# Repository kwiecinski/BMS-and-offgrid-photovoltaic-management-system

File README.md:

# Offgrid Photovoltaic Management System 
 ### Project contains:
 #### A. Power and mechanical part:

  1. [ Photovoltaic modules](#1-photovoltaic-modules)  
  2. [ Concrete base mounting](#2-concrete-base-mounting)  
  3. [ Metalworking and welding mounting bases and angle bar](#3-metalworking-and-welding-mounting-bases-and-angle-bar)  
  4. [ Painting mounting base, angle bars and perforated profiles](#4-painting-mounting-base-angle-bars-and-perforated-profiles)  
  5. [ PV mountings to perforated profiles](#5-pv-mountings-to-perforated-profiles)  
  6. [ Assembly of PV installation](#6-assembly-of-pv-installation)  
  7. [ Fully assembled PV installation](#7-fully-assembled-pv-installation)<br>
  8. [ Underground Cable Installation and Connection to the Building](#8-underground-cable-installation-and-connection-to-the-building)
 
B. [EASUN inverter - description, installation schematic and wiring](#easun-inverter---description-installation-and-wiring)
#### C. Managemenet system part:
- [BMS for lead-acid batteries](#bms-for-lead-acid-batteries) - equalize battery, protect from large charge/discharge currents, montors battery state (temp, voltage)
- [ESP32 Master module](#esp32-master-module) - it communicate with EASUN  converter, BMS, Homa Assistant, Energy Meters and sensor. Supervise all system work propertly.
- [Home Assistant integration](#home-assistant-integration) - integrate ESP Master module with HA for easy and compact managment (local and remote access)
- [Power Tracking module](#power-tracking-module) - it is used to regulate heater power accordingly to avaible energy from PV

## PV panels connection and DIY Ground Mount structure 

### 1. Photovoltaic modules
The photovoltaic modules I used in my PV installation are Trina Solar TSM-245. These are used panels that I purchased for around $40 each. The installation consists of 8 modules connected in series.

[📄 **Trina Solar TSM-245 datasheet**](docs/datasheets/TSM-PC05_trinasolar.pdf)

<table>
  <tr>
    <td align="center">
      <br />
      <sub>PV module TSM-245 - technical data</sub>
    </td>
    <td align="center">
      <br />
      <sub>PV module TSM-245 - internal diode wiring</sub>
    </td>
  </tr>
</table>

<table>
  <tr>
    <td align="center">
      <br />
      <sub>PV module TSM-245 - front</sub>
    </td>
    <td align="center">
      <br />
      <sub>PV module TSM-245 - back</sub>
    </td>
  </tr>
</table>

The first stage was marking the mounting points for the mouting base structure. The entire construction has eight support points. After digging holes in the ground, they were filled with concrete, and concrete bases with reinforcement were embedded in them. I had plenty of these as production waste from the company where I work. They are typically used for mounting lightning protection masts on flat building roofs.

Inside each base, there is reinforcement and four M16 threads. I modified the bases by drilling holes on the opposite side, and I welded additional reinforcement to the bottom using scrap metal, which helps to improve the structural stability.

Before mounting the structure to the concrete bases, the contact surfaces were coated with a bituminous compound to prevent corrosion.

### 2. Concrete base mounting

<table>
  <tr>
    <td align="center" colspan="2">
      <br />
      <sub>Concrete base with reinforcement</sub>
    </td>
  </tr>
  <tr>
    <td align="center">
      <br />
      <sub>Concrete base with mounting thread</sub>
    </td>
    <td align="center">
      <br />
      <sub>Concrete base with bitumen</sub>
    </td>
  </tr>
</table>
<br>

Visible in the photo below is a set of four steel mounting bases of varying heights, with welded pipes and mounting plates. Each element was made with consideration for uneven ground, that is why there are different pipe lengths. Each base has a bottom plate with holes for M16 bolts, intended for anchoring to a concrete base. On the table next to them lies a long steel angle bar, which was welded from several sections. After welding, the elements were ground down. The photo was taken after the mechanical work was completed, during surface preparation for painting. 
All the steel used for building the PV mouting structure comes from scrap yard.

### 3. Metalworking and welding mounting bases and angle bar
<br>
<table>
  <tr>
    <td align="center" colspan="2">
      <br />
      <sub>Metalworking and welding mounting bases and angle bar</sub>
    </td>
  </tr>
  <tr>
    <td align="center" colspan="2">
      <br />
      <sub>Steel angle bar before painting</sub>
    </td>
  </tr>
    <tr>
    <td align="center" colspan="2">
      <br />
      <sub>Longer mounting base  while painting</sub>
    </td>
  </tr>
</table>

Longer mounting base are responsible for the solar incidence angle which in this case is 40 degrees
### 4. Painting mounting base, angle bars and perforated profiles
<table>
  <tr>
    <td align="center" colspan="2">
      <a href="docs\photos\ground-mount-structure\steel-workshop-and-painting-11.jpg">
        
      <div style="width: 200px;">
        
        <div style="text-align: center;">
          <sub>Shorter and longer mounting base after painting</sub>
        </div>
      </div>
    </td>
  </tr>
  <tr>
    <td colspan="2" style="text-align: left;">
      <div style="width: 410px;">
        
        <div style="text-align: center;">
          <sub>Shorter mounting base after painting</sub>
        </div>
      </div>
    </td>
  </tr>
  <tr>
    <td colspan="2" style="text-align: left;">
      <div style="width: 410px;">
        
        <div style="text-align: center;">
          <sub>Perforated profiles, often used for fixing cable tray systems, <br>turned out to be ideal as internal panel brackets. <br>Since they are galvanized, they must be painted <br>with zinc-compatible paint.</sub>
        </div>
      </div>
    </td>
  </tr>
  <tr>
    <td colspan="2" style="text-align: left;">
      <div style="width: 410px;">
        
        <div style="text-align: center;">
          <sub>Longer mounting bases drying after painting</sub>
        </div>
      </div>
    </td>
  </tr>
</table>

### 5. PV Mountings to perforated profiles

<table>
  <tr>
    <td colspan="2" style="text-align: left;">
      <div style="width: 410px;">
        
        <div style="text-align: center;">
          <sub>Sheet metal used to prepare panel mounts for perforated profiles</sub>
        </div>
      </div>
    </td>
  </tr>

  <tr>
    <td colspan="2" style="text-align: left;">
      <div style="width: 410px;">
        
        <div style="text-align: center;">
          <sub>Panel mounts for perforated profiles before welding and drilling</sub>
        </div>
      </div>
    </td>
  </tr>

  <tr>
    <td colspan="2" style="text-align: left;">
      <div style="width: 410px;">
        
        <div style="text-align: center;">
          <sub>Panel mounts for perforated profiles. The central M10 bolt is used to attach to the perforated profile, and the two M8 holes are for screwing PV panels</sub>
        </div>
      </div>
    </td>
  </tr>

  <tr>
    <td colspan="2" style="text-align: left;">
      <div style="width: 410px;">
        
        <div style="text-align: center;">
          <sub>Solar panel mounting elements after painting, drying in progress</sub>
        </div>
      </div>
    </td>
  </tr>

  <tr>
    <td colspan="2" style="text-align: left;">
      <div style="width: 410px;">
        
        <div style="text-align: center;">
          <sub>Spacer for mounting solar panels to the perforated panels which are on the outer side of mounting structure</sub>
        </div>
      </div>
    </td>
  </tr>

  <tr>
    <td colspan="2" style="text-align: left;">
      <div style="width: 410px;">
        
        <div style="text-align: center;">
          <sub>Solar panel mounts for perforated profiles – painted and drying</sub>
        </div>
      </div>
    </td>
  </tr>

  <tr>
    <td colspan="2" style="text-align: left;">
      <div style="width: 410px;">
        
        <div style="text-align: center;">
          <sub>Solar panel mounts for perforated profiles</sub>
        </div>
      </div>
    </td>
  </tr>
</table>

### 6. Assembly of PV installation
<table>
  <tr>
    <td colspan="2" style="text-align: left;">
      <div style="width: 410px;">
        
        <div style="text-align: center;">
          <sub>Shorter mounting bases and angle bar mounted on concrete bases. Thanks to the height difference of the mounting bases, the angle bar remains level</sub>
        </div>
      </div>
    </td>
  </tr>
  <tr>
    <td colspan="2" style="text-align: left;">
      <div style="width: 410px;">
        
        <div style="text-align: center;">
          <sub>Shorter mounting base mounted on a concrete base. Before installation, the base was coated with a bituminous compound. Stainless steel bolts were used for assembly</sub>
        </div>
      </div>
    </td>
  </tr>
  <tr>
    <td colspan="2" style="text-align: left;">
      <div style="width: 410px;">
        
        <div style="text-align: center;">
          <sub>Ground mounting structure ready for PV panel installation</sub>
        </div>
      </div>
    </td>
  </tr>
  <tr>
    <td colspan="2" style="text-align: left;">
      <div style="width: 200px;">
        
        <div style="text-align: center;">
          <sub>Here you can see how the panel mounts are used to connect solar panel with perforated profile</sub>
        </div>
      </div>
    </td>
  </tr>
</table>

### 7. Fully assembled PV installation
<table>
    <tr>
    <td align="center" colspan="2">
      <br />
      <sub>Fully assembled PV installation - front</sub>
    </td>
  </tr>
    </tr>
    <tr>
    <td align="center" colspan="2">
      <br />
      <sub>Fully assembled PV installation - back<sub>
    </td>
  </tr>
</table>

### 8. Underground Cable Installation and Connection to the Building
To connect the panels, I used AsXSn 4x35 cable and additionally laid an AsXSn 4x25 cable. I found these cables at a scrapyard at a good price, which is why I chose this somewhat unconventional option. Additionally, I installed a gel-filled Ethernet twisted pair cable to allow for potential data transmission if needed.

<table>
  <tr>
    <td align="center">
      <br />
      <div style="max-width: 200px; text-align: center;">
        <sub>Underground cable entry to the building</sub>
      </div>
    </td>
  </tr>

  <tr>
    <td align="center" valign="top">
      <br />
      <div style="max-width: 200px; text-align: center;">
        <sub>Cable entry point inside the building</sub>
      </div>
    </td>
    <td align="center" valign="top">
      <br />
      <div style="max-width: 200px; text-align: center;">
        <sub>Close-up of the conduit connection and grounding wire</sub>
      </div>
    </td>
  </tr>
</table>

To connect the AROT 50 (blue) protective pipe with the RL50 pipe (white), I created an adapter using a 3D printer. PETG material was chosen for its weather resistance. The opening in adapter was designed to fit the protective pipe only after heating the adapter. Once cooled, the adapter holds the pipe in place.

<table>
  <tr>
    <td align="center" colspan="2">
      <br/>
      <sub>Adapter 3D model</sub>
    </td>
  </tr>

  <tr>
    <td align="center">
      <br/>
      <sub>Adapter after printing</sub>
    </td>
    <td align="center ">
      <br/>
      <sub>Adapter mounted on protective pipe</sub>
    </td>
  </tr>

  <tr>
    <td align="center" colspan="2">
      <br />
      <sub>Junction box inside the building.<br> Visible screw terminals for two cables, twisted pair Ethernet connection, <br>and additional grounding.</sub>
    </td>
  </tr>
    <tr>
    <td align="center" colspan="2">
      <br />
      <sub>Junction box at the PV installation site.</sub>
    </td>
  </tr>
</table>

## EASUN inverter - Description, installation and wiring

[📄 **EASUN ISolar SMG II 4kW datasheet**](docs/ISolar-SMG-II-4KW-WiFi.pdf) <br><br>
The EASUN ISolar SMG II 4kW is an off-grid inverter. It does not have the capability to synchronize with the power grid.

Inverter specifications:
- Input voltage from PV array: 60-500V DC
- Input current from PV array: 15A
- Output voltage: 230V/50Hz
- Battery voltage: 24V
- Battery current: max 100A

In my case, 12 PV were connected, each with a maximum voltage of 37V, resulting in a maximum voltage of approximately 440V.

The maximum current of the PV array is 8A.  
Connected PV array meet the inverter's specifications.

Power Source Priority

| Option       | Description       |
|-----------------|-----------------|
| SOL | The inverter uses solar energy to power the loads. If solar energy is insufficient to meet the load demand, the battery **only supplements** the power. The grid supplies power to the loads only when: Solar energy is unavailable (e.g., at night or during heavy cloud cover). Battery voltage drops to the low-level warning voltage or the threshold set in Program 12.|
| UFI  | Utility will provide power to the loads as first priority. Solar and battery energy will provide power to the loads only when utility power is notavailable.|
| SBU  | The inverter uses solar energy to power the loads. If solar energy is insufficient, the battery provides power to the loads.​ The grid supplies power to the loads only when the battery voltage drops to the low-level warning voltage or the threshold set in Program 12. |
| SUB  | Solar energy is charged first and then power to the loads. If solar energy is not sufficient to power all connected loads, Utility energy will supply power to the loads at the same time. <br>**Attention**: I found that there is an idle power (about 150W) that must be drawn from the grid before parallel operation of the grid + solar energy can occur. This means that if the power consumption is up to 150W, it will not be supplied by solar energy but by the grid. If power consumption is over 150W eg. 500W then 350W will we drawn from solar and still 150W will be drawn from grid.|

Key Differences between SOL and SBU is battery usage:

SOL Mode: The battery assists only when solar energy is insufficient, and the grid is used if both solar and battery cannot meet the load. 

SBU Mode: The battery is used after solar, and the grid is used only when the battery is depleted.​

# Management System diagram:

## BMS for lead-acid batteries
BMS have several tasks:
- Battery Balancer equalizes the state of charge of two series connected 12V batteries. If one of battery is overcharged it discharge it using resistor.
- Bidirectional DC-DC converter - protect battery from too much discharge or charge current
- Battery monitoring - measurment of temperature of each battery and voltage.

The BMS is controlled by an AVR64DD28 microcontroller. To program it, you need a programmer that supports UPDI.
I'm using SerialUPDI (a modified version with high-voltage programming capability and galvanic isolation, which you can find here: SerialUPDI link).

To measure battery voltage and current, I use the INA226 sensor along with the built-in ADC of the microcontroller.

The INA226 measures:

- The voltage of the entire battery pack, split into BATT_LOW (bottom battery) and BATT_HIGH (top battery)

- The voltage across a shunt resistor, used to measure the current flowing through the entire pack

Since the INA226 is bidirectional, it allows both charging and discharging current measurements.

The microcontroller’s ADC measures only BATT_LOW voltage.
By subtracting the ADC reading from the INA226’s total voltage reading, I can calculate the BATT_HIGH voltage.

Cell balancing is performed using high-power resistors, each connected in parallel with a battery cell.
Each resistor is switched by a MOSFET, which is controlled by the MCU using PWM.

PWM is hardware-generated using the TCD timer, which controls two outputs: WOA and WOB, each assigned to a specific MCU pin.

The TCD timer is capable of generating...

## ESP32 Master module

## Home Assistant integration

## Power Tracking module

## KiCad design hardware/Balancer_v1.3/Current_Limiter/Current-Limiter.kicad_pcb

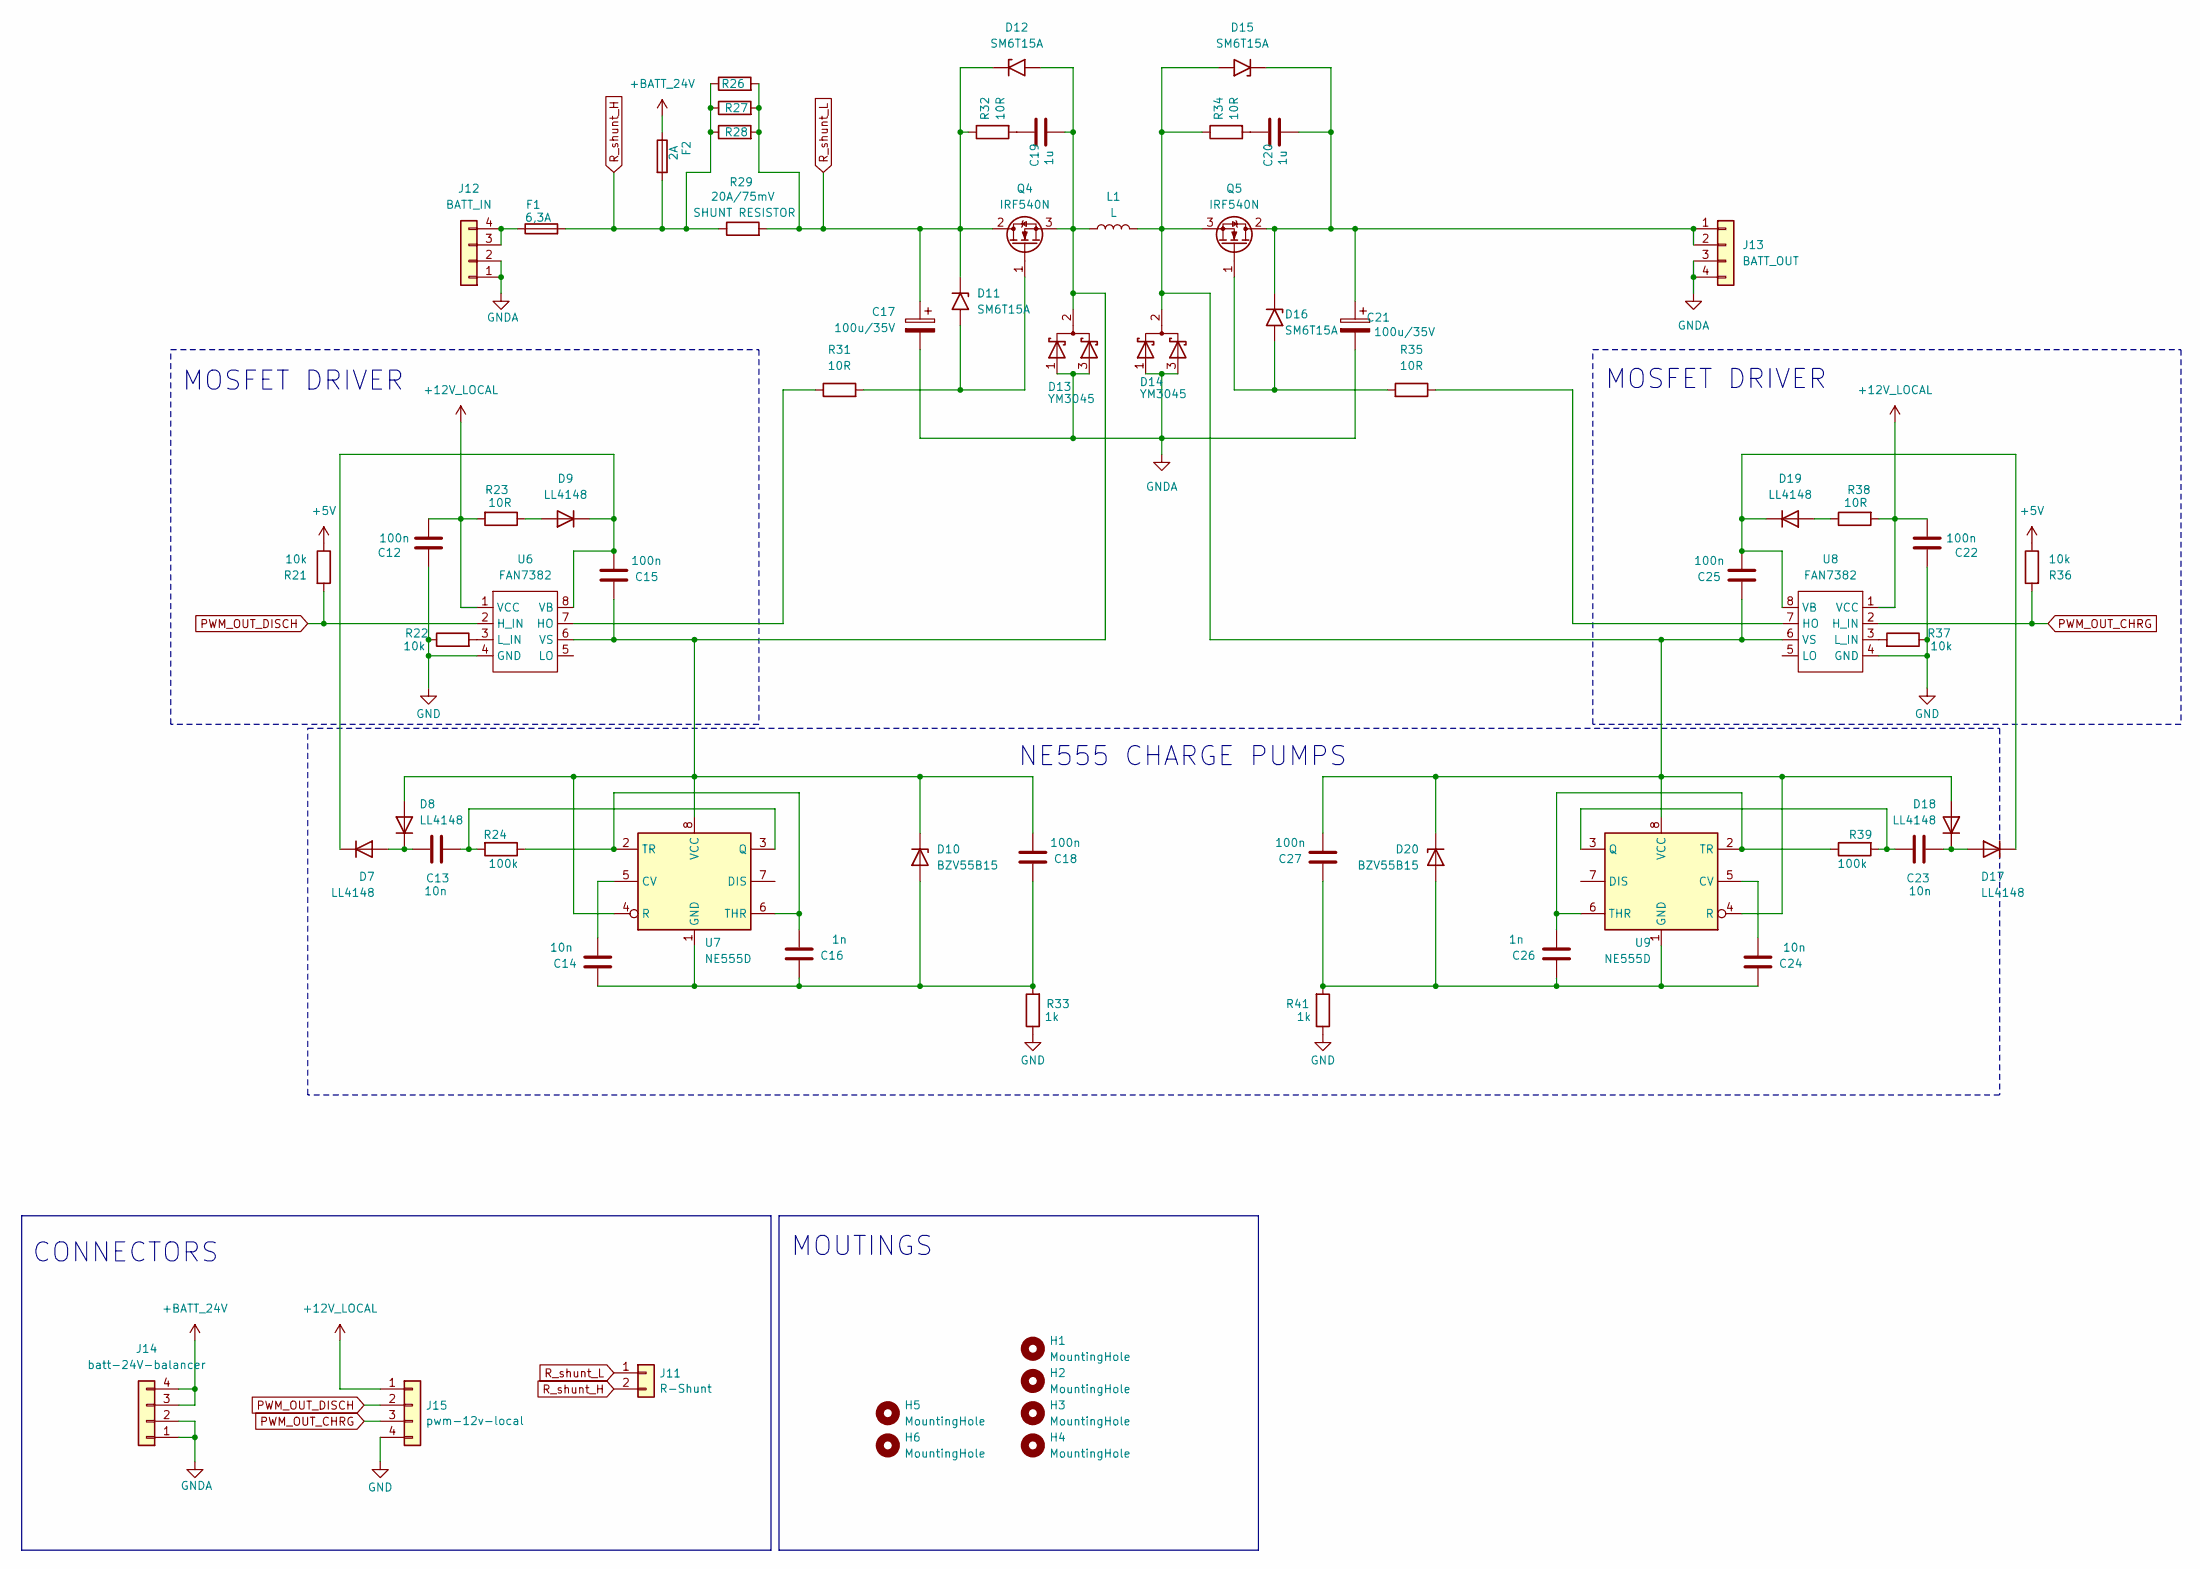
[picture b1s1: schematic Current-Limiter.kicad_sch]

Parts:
C12, C15, C18, C22, C25, C27: 100n; C_0805_2012Metric_Pad1.18x1.45mm_HandSolder
C13, C14, C23, C24: 10n; C_0805_2012Metric_Pad1.18x1.45mm_HandSolder
C16, C26: 1n; C_0805_2012Metric_Pad1.18x1.45mm_HandSolder
C17, C21: 100u/35V; CP_Radial_D16.0mm_P7.50mm
C19, C20: 1u; C_Disc_D5.0mm_W2.5mm_P2.50mm
D7, D8, D9, D17, D18, D19: LL4148; D_MiniMELF
D10, D20: BZV55B15; D_MiniMELF
D11, D12, D15, D16: SM6T15A; D_SMB
D13, D14: YM3045; TO-220-3_V_Thick_Pads
F1: 6,3A; Fuse_Blade_ATO_directSolder
F2: 2A; Fuseholder_Clip-5x20mm_Eaton_1A5601-01_Inline_P20.80x6.76mm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
H1, H2, H3, H4, H5, H6: MountingHole; Mount-Hole-3mm
J11: R-Shunt; PinHeader_1x02_P2.54mm_Vertical
J12: BATT_IN; Flat-6,3mm-connector-4P
J13: BATT_OUT; Flat-6,3mm-connector-4P
J14: batt-24V-balancer; PinSocket_1x04_P2.54mm_Vertical
J15: pwm-12v-local; PinSocket_1x04_P2.54mm_Vertical
L1: L; Inductor_Toroidal
Q4, Q5: IRF540N; TO-220-3_V_Thick_Pads
R21, R22, R36, R37: 10k; R_0805_2012Metric
R23, R31, R35, R38: 10R; R_0805_2012Metric
R24, R39: 100k; R_0805_2012Metric
R26, R27, R28: 20A/75mV; R_Axial_DIN0309_L9.0mm_D3.2mm_P20.32mm_Horizontal
R29: 20A/75mV; Resistor-Power-5W-L22-W10
R32, R34: 10R; R_Axial_DIN0204_L3.6mm_D1.6mm_P7.62mm_Horizontal
R33, R41: 1k; R_0805_2012Metric
U6, U8: FAN7382; DIP-8_W10.16mm_LongPads
U7, U9: NE555D; SOIC-8_3.9x4.9mm_P1.27mm

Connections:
+5V: R21.1, R36.1
+12V_LOCAL: C12.2, C22.2, J15.1, R23.2, R38.2, U6.1 (VCC), U8.1 (VCC)
+BATT_24V: F2.1, J14.3, J14.4
GND: C12.1, C22.1, J15.4, R22.1, R33.1, R37.1, R41.1, U6.4 (GND), U8.4 (GND)
GNDA: C17.2, C21.2, D13.1 (K), D13.3 (K), D14.1 (K), D14.3 (K), J12.1, J12.2, J13.3, J13.4, J14.1, J14.2
unnamed: C19.1, R32.2
unnamed: C20.1, R34.2
unnamed: C13.2, D7.2 (A), D8.1 (K)
unnamed: C15.2, D7.1 (K), D9.1 (K), U6.8 (VB)
unnamed: D9.2 (A), R23.1
unnamed: C14.1, C16.1, C18.1, D10.2 (A), R33.2, U7.1 (GND)
unnamed: C15.1, C18.2, C19.2, D8.2 (A), D10.1 (K), D12.2 (A2), D13.2 (A), L1.1, Q4.3 (S), U6.6 (VS), U7.4 (R), U7.8 (VCC)
unnamed: D11.2 (A2), Q4.1 (G), R31.2
unnamed: C25.1, C27.2, D14.2 (A), D15.2 (A2), D18.2 (A), D20.1 (K), L1.2, Q5.3 (S), R34.1, U8.6 (VS), U9.4 (R), U9.8 (VCC)
unnamed: C20.2, C21.1, D15.1 (A1), D16.1 (A1), J13.1, J13.2, Q5.2 (D)
unnamed: D16.2 (A2), Q5.1 (G), R35.2
unnamed: C23.2, D17.2 (A), D18.1 (K)
unnamed: C25.2, D17.1 (K), D19.1 (K), U8.8 (VB)
unnamed: D19.2 (A), R38.1
unnamed: C24.1, C26.1, C27.1, D20.2 (A), R41.2, U9.1 (GND)
unnamed: F1.1, J12.3, J12.4
unnamed: R31.1, U6.7 (HO)
unnamed: R22.2, U6.3 (L_IN)
unnamed: C14.2, U7.5 (CV)
unnamed: C13.1, R24.2, U7.3 (Q)
unnamed: C16.2, R24.1, U7.2 (TR), U7.6 (THR)
unnamed: R35.1, U8.7 (HO)
unnamed: R37.2, U8.3 (L_IN)
unnamed: C24.2, U9.5 (CV)
unnamed: C23.1, R39.2, U9.3 (Q)
unnamed: C26.2, R39.1, U9.2 (TR), U9.6 (THR)
PWM_OUT_CHRG: J15.3, R36.2, U8.2 (H_IN)
PWM_OUT_DISCH: J15.2, R21.2, U6.2 (H_IN)
R_shunt_H: F1.2, F2.2, J11.2, R26.1, R27.1, R28.1, R29.1
R_shunt_L: C17.1, D11.1 (A1), D12.1 (A1), J11.1, Q4.2 (D), R26.2, R27.2, R28.2, R29.2, R32.1

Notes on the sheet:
MOUTINGS
NE555 CHARGE PUMPS
MOSFET DRIVER
CONNECTORS

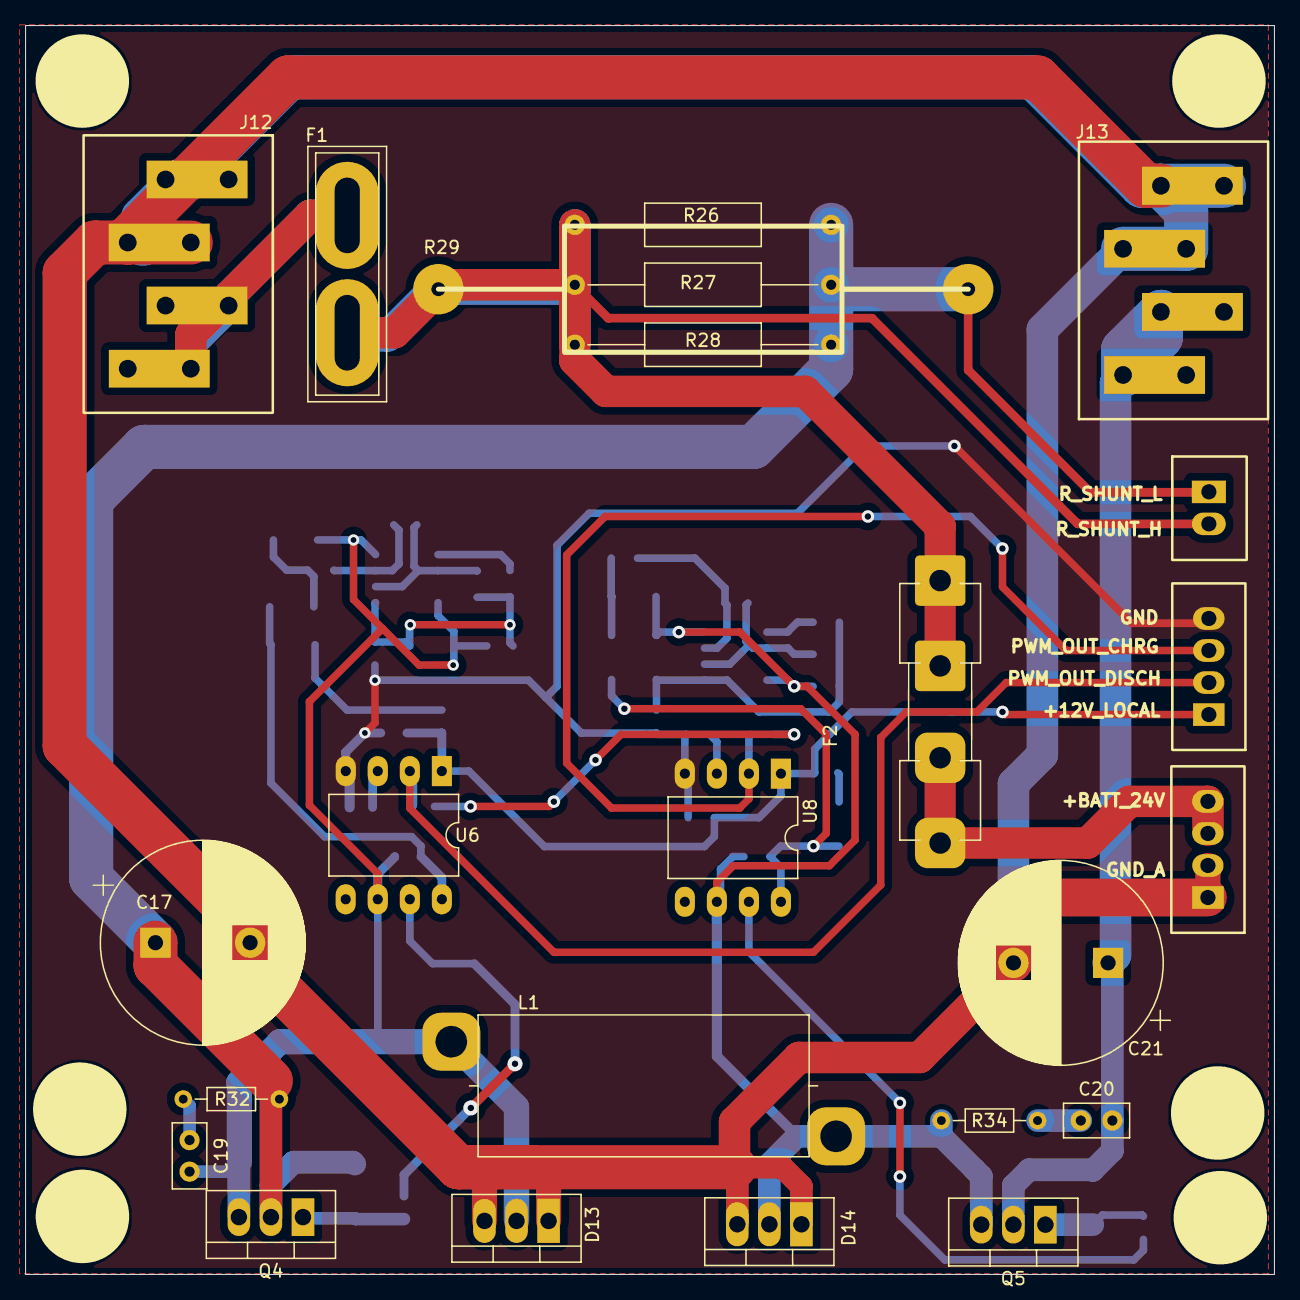
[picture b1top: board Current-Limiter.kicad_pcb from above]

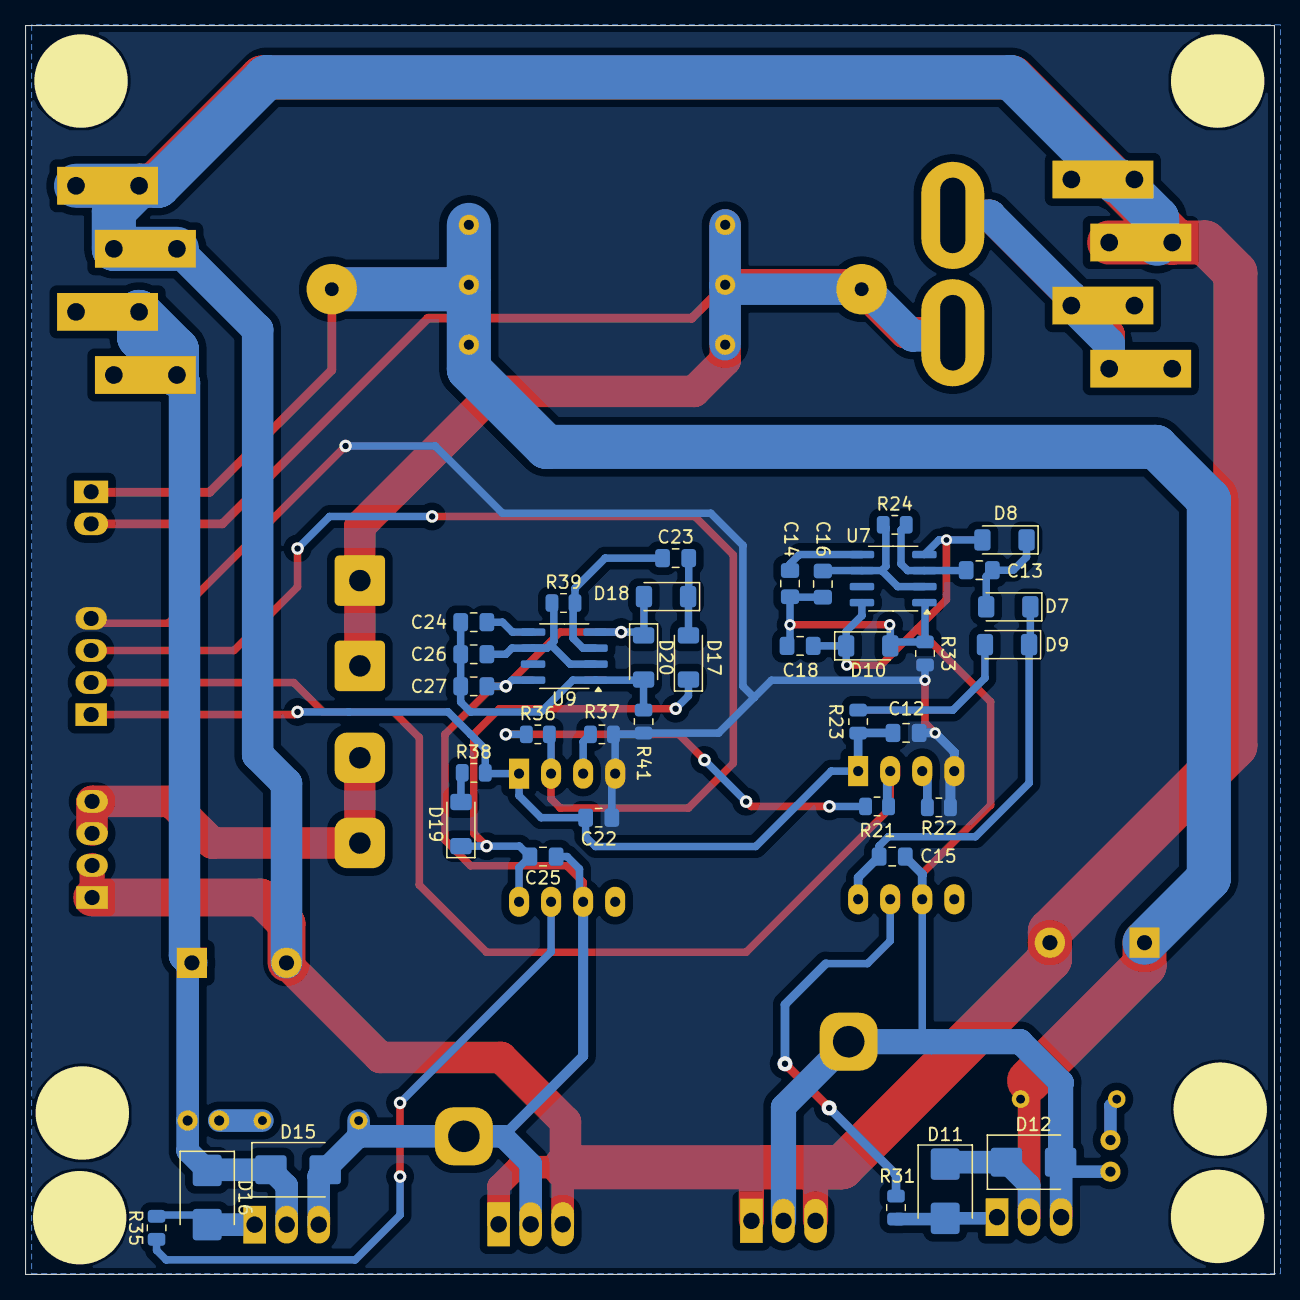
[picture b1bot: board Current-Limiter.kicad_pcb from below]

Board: 2 copper layers, 99.0 x 99.0 mm, 68 parts (38 on the bottom side), 35 nets.

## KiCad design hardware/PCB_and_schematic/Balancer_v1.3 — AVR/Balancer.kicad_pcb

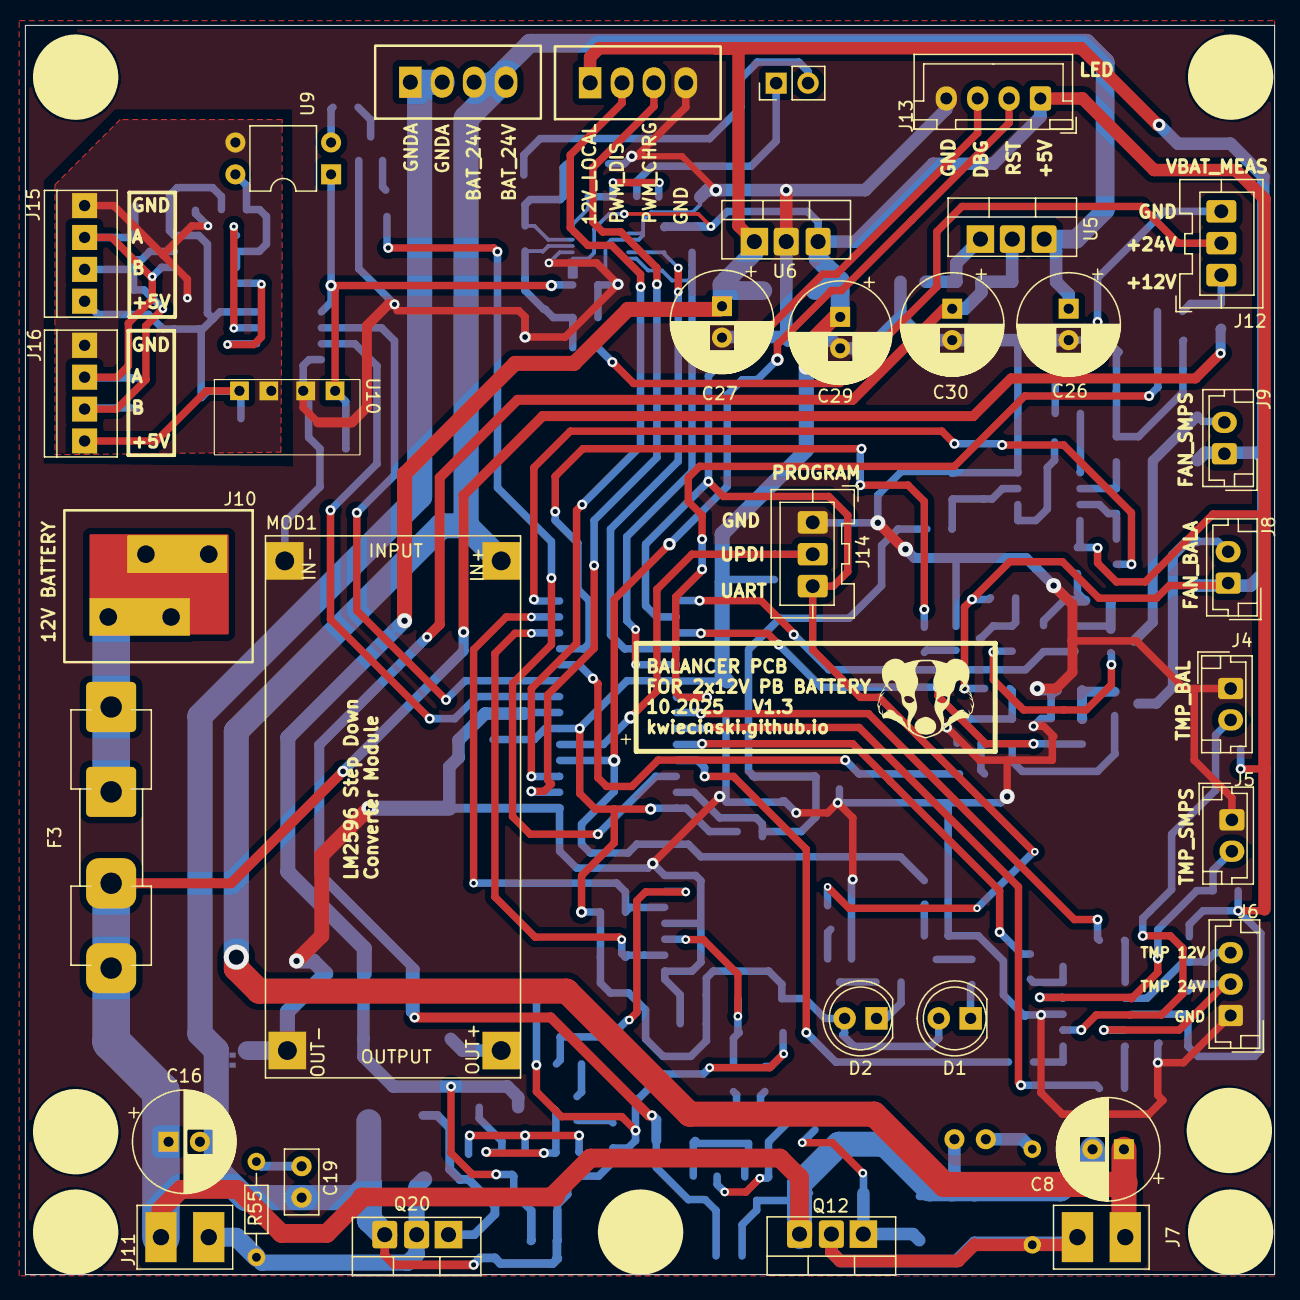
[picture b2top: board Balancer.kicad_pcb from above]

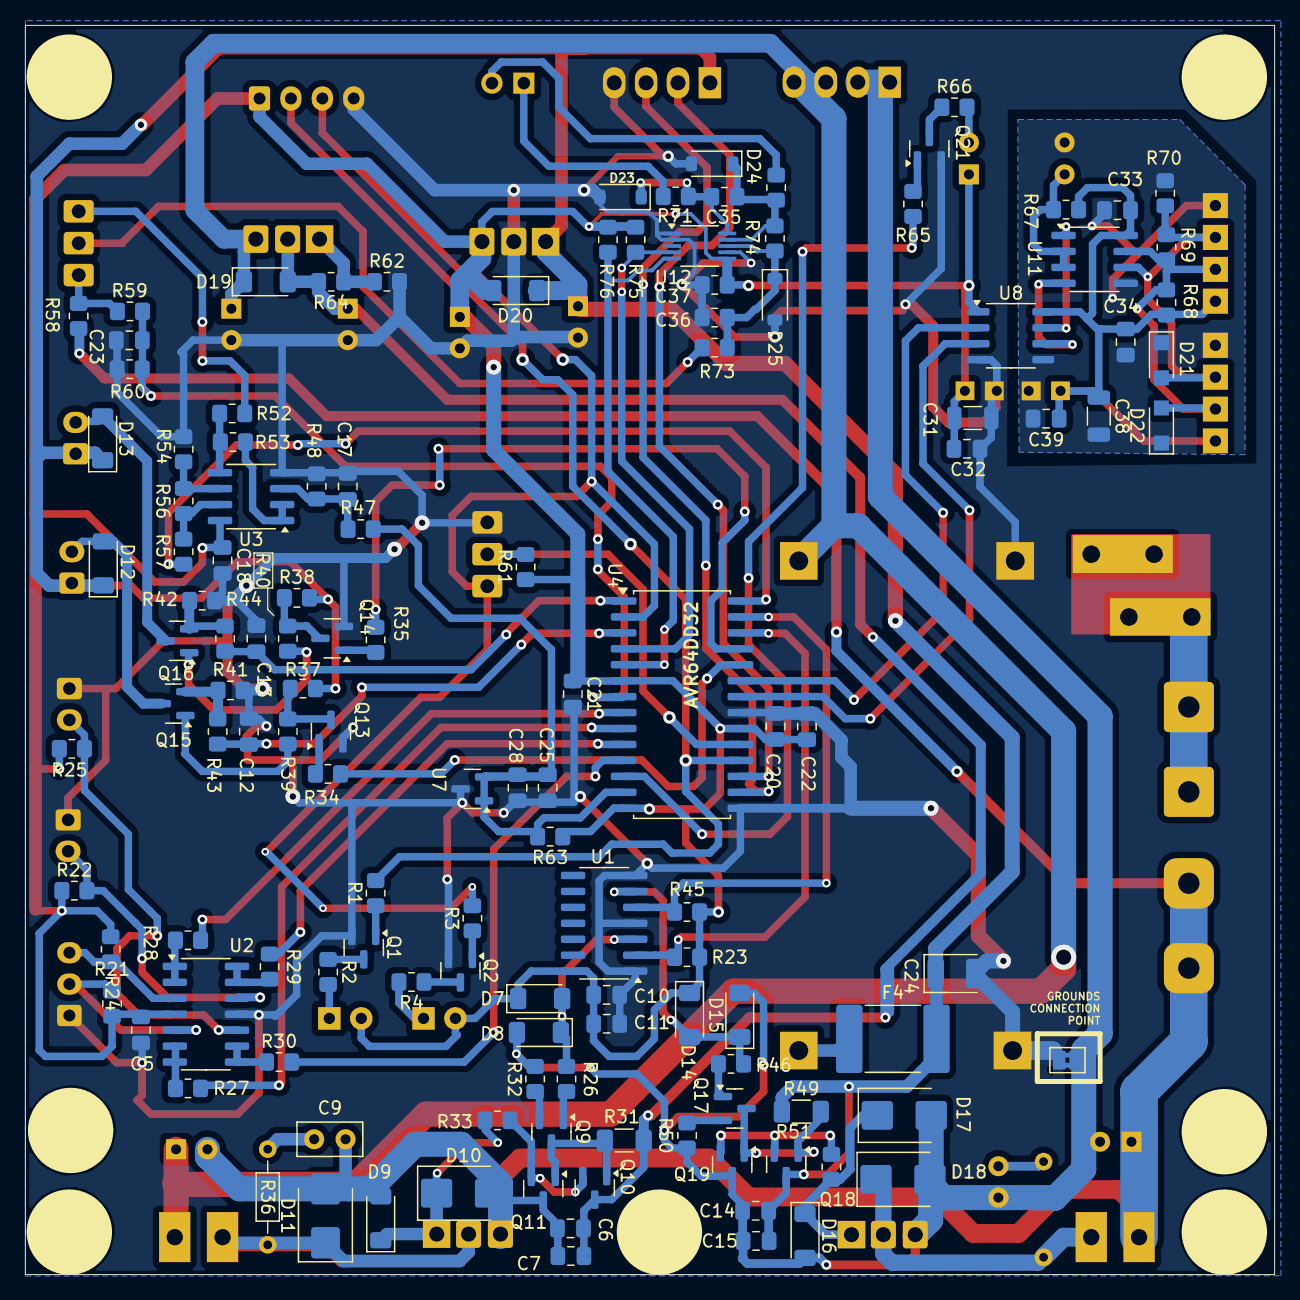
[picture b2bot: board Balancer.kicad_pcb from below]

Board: 2 copper layers, 99.5 x 99.5 mm, 170 parts (129 on the bottom side), 96 nets.

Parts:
C5, C6, C10, C14, C17, C18, C20, C21, C28, C32, C33, C34, C39: 100n; C_0805_2012Metric_Pad1.18x1.45mm_HandSolder
C7, C15, C22, C25: 10u; C_0805_2012Metric_Pad1.18x1.45mm_HandSolder
C8, C16: 470u/25V; CP_Radial_D8.0mm_P2.50mm
C9, C19: 1u; C_Disc_D5.0mm_W2.5mm_P2.50mm
C11: 1u; C_0805_2012Metric_Pad1.18x1.45mm_HandSolder
C12, C13: 47n; C_0805_2012Metric_Pad1.18x1.45mm_HandSolder
C23: 470n; C_0805_2012Metric_Pad1.18x1.45mm_HandSolder
C24: 100u/6,3V (JA8); CP_EIA-3528-21_Kemet-B
C26: 220u/35V; CP_Radial_D8.0mm_P2.50mm
C27: 470u/16V; CP_Radial_D8.0mm_P2.50mm
C29: 220u/6,3V; CP_Radial_D8.0mm_P2.50mm
C30: 100u/25V; CP_Radial_D8.0mm_P2.50mm
C31, C38: 10u; C_1206_3216Metric
C35, C36, C37: 100n; R_0805_2012Metric_Pad1.20x1.40mm_HandSolder
D1, D2: LED; LED_D5.0mm
D7, D8, D9, D12, D13, D14, D15, D16: BAT86; D_MiniMELF
D10, D11, D17, D18: SM6T15A; D_SMB
D19, D20: 1N4148; D_MiniMELF
D21, D22: D_TVS; Nexperia_CFP3_SOD-123W
D23, D24, D25: PTVS5V0Z1USK; D_SOD-123
F3: 6,3A; Fuseholder_Clip-5x20mm_Eaton_1A5601-01_Inline_P20.80x6.76mm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
F4: 2A; Fuse_2920_7451Metric_Pad2.10x5.45mm_HandSolder
H1, H3, H4, H5, H7, H9, H10: MountingHole; Mount-Hole-3mm
J1: batt-24V-balancer; PinSocket_1x04_P2.54mm_Vertical
J2: pwm-12v-local; PinSocket_1x04_P2.54mm_Vertical
J3: R-Shunt; PinHeader_1x02_P2.54mm_Vertical
J4: TMP_BALANCER; JST_EH_B2B-EH-A_1x02_P2.50mm_Vertical
J5: TMP_SMPS; JST_EH_B2B-EH-A_1x02_P2.50mm_Vertical
J6: THERMISTOR_BATT; JST_EH_B3B-EH-A_1x03_P2.50mm_Vertical
J7, J11: LOAD_RESISTOR; Conn_1x2_wire
J8: FAN_BALANCER; JST_EH_B2B-EH-A_1x02_P2.50mm_Vertical
J9: FAN_SMPS; JST_EH_B2B-EH-A_1x02_P2.50mm_Vertical
J10: BATT_12V; Flat-6,3mm-connector-2P
J12: V_MEAS; JST_XA_1x03_P2.54mm_Vertical
J13: LED; JST_XH_B4B-XH-A_1x04_P2.50mm_Vertical
J14: ICP; JST_XA_1x03_P2.54mm_Vertical
J15, J16: RS485; Conn-01x04-N25-W4P
JP1: GND_Bridged; SolderJumper-2_P1.3mm_Bridged2Bar_Pad1.0x1.5mm
MOD1: LM2596-Step-Down; LM2596-Step-Down-Conv
Q1, Q2, Q9, Q10, Q13, Q14, Q17, Q18, Q21: BC817; SOT-23
Q11, Q19: BC807; SOT-23
Q12, Q20: IRF540N; TO-220-3_Vertical-little-bigger pads
Q15, Q16: AO3400A; SOT-23
R1, R3: 10K; R_0805_2012Metric_Pad1.20x1.40mm_HandSolder
R2, R4, R50: 220R; R_0805_2012Metric_Pad1.20x1.40mm_HandSolder
R21, R22, R24, R25: 150k; R_0805_2012Metric_Pad1.20x1.40mm_HandSolder
R23, R34, R35, R37, R38, R45, R61, R75, R76: 10k; R_0805_2012Metric_Pad1.20x1.40mm_HandSolder
R26, R27, R28, R29, R30, R43, R44, R46, R60, R62, R64, R65, R66: 1k; R_0805_2012Metric_Pad1.20x1.40mm_HandSolder
R31, R49: 2k2; R_1206_3216Metric_Pad1.30x1.75mm_HandSolder
R32: 470R; R_0805_2012Metric_Pad1.20x1.40mm_HandSolder
R33, R51, R71, R72, R73: 10R; R_0805_2012Metric_Pad1.20x1.40mm_HandSolder
R36, R55: 10R; R_Axial_DIN0204_L3.6mm_D1.6mm_P7.62mm_Horizontal
R39, R40, R57: 100R; R_0805_2012Metric_Pad1.20x1.40mm_HandSolder
R41, R42: 210mR; R_0805_2012Metric_Pad1.20x1.40mm_HandSolder
R47, R48, R52, R53, R54, R56: 10k/1%; R_0805_2012Metric_Pad1.20x1.40mm_HandSolder
R58, R74: 0R; R_0805_2012Metric_Pad1.20x1.40mm_HandSolder
R59: 6k8; R_0805_2012Metric_Pad1.20x1.40mm_HandSolder
R63, R68, R70: 510R; R_0805_2012Metric_Pad1.20x1.40mm_HandSolder
R67: 4k7; R_0805_2012Metric_Pad1.20x1.40mm_HandSolder
R69: 120R; R_0805_2012Metric_Pad1.20x1.40mm_HandSolder
U1: 74AHCT125; SOIC-14_3.9x8.7mm_P1.27mm
U2: LM324; SOIC-14_3.9x8.7mm_P1.27mm
U3: LMV358; SOIC-8_3.9x4.9mm_P1.27mm
U4: AVR64DD28; SOIC-28W_7.5x17.9mm_P1.27mm
U5: LM317_TO-220; TO-220-3_Vertical-little-bigger pads
U6: LM7805_TO220; TO-220-3_Vertical-little-bigger pads
U7: TL432DBZ; SOT-23
U8: ADUM3211ARZ; SO-8_3.9x4.9mm_P1.27mm
U9: PC817; DIP-4_W7.62mm
U10: B0505S-1W; B0505S
U11: ST485; SOIC-8_3.9x4.9mm_P1.27mm
U12: INA226; VSSOP-10_3x3mm_P0.5mm

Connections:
+5V: C5.1, C10.1, C11.1, C18.1, C20.1, C21.1, C22.1, C29.1, C31.1, C32.1, C37.1, D1.2 (A), D2.2 (A), D7.1 (A1), D14.1 (A1), D20.2 (A), J13.1, R21.1, R22.1, R23.1, R24.1, R25.1, R45.1, R61.1, R63.1, R75.1, R76.1, U1.14 (VCC), U2.4 (V+), U3.8 (V+), U4.6 (VDDIO2), U4.14 (VDD), U4.20 (VDD), U6.3 (VO), U8.1 (VDD1), U9.1, U10.1 (GND), U12.6 (VS)
+5V_RS485: C33.1, C34.1, C38.1, C39.1, J15.1, J16.1, R67.1, R68.1, U8.8 (VDD2), U10.4 (VOUT), U11.8 (VCC)
+12V_LOCAL: C14.1, C15.1, C24.1, C27.1, D12.1 (A1), D13.1 (A1), D20.1 (K), F4.2, J2.1, J8.1, J9.1, Q18.3 (C), R37.2, R38.2, R49.1, U6.1 (VI)
+24V_LOCAL: C6.1, C7.1, C30.1, D19.2 (A), Q10.3 (C), R31.1, R64.2, U5.2 (VO)
+BATT_12V: C6.2, C7.2, C8.2, C9.2, C16.1, D9.2 (A2), D10.2 (A2), D11.2 (A2), F3.1, J11.1, Q11.3 (C), Q12.3 (S), R58.1
+BATT_24V: C8.1, C26.1, D19.1 (K), J1.3, J1.4, J7.1, MOD1.2 (IN+), U5.3 (VI)
/BMS_microcontroller/RS485_A: D21.2 (A2), J15.3, J16.3, R69.2, R70.1, U11.6 (A)
/BMS_microcontroller/RS485_B: D22.2 (A2), J15.2, J16.2, R68.2, R69.1, U11.7 (B)
/BMS_microcontroller/VOLTAGE_BATT_12V_3W: J12.1, R58.2, R59.1
ADC_I_FAN1: C13.2, R44.2, U4.1 (PA7)
ADC_I_FAN2: C12.2, R43.2, U4.3 (PC1)
BALANCE_ON_12V: R45.2, U1.5, U4.27 (PA5)
BALANCE_ON_24V: R23.2, U1.2, U4.26 (PA4)
CLOCK: R76.2, U4.5 (PC3), U12.5 (SCL)
DBG_UART: J13.3, J14.3, R3.2, U4.2 (PC0)
GND: C5.2, C10.2, C11.2, C12.1, C13.1, C17.2, C18.2, C20.2, C21.2, C22.2, C23.2, C24.2, C25.2, C26.2, C27.2, C28.2, C29.2, C30.2, C31.2, C32.2, C36.2, C37.2, D23.2 (A), D24.2 (A), D25.2 (A), J2.4, J4.1, J5.1, J6.1, J13.4, J14.1, JP1.1 (A), MOD1.1 (IN-), MOD1.3 (OUT-), Q1.2 (E), Q2.2 (E), Q13.2 (E), Q14.2 (E), Q21.2 (E), R41.2, R42.2, R48.2, R54.2, R60.2, R62.2, U1.1, U1.4, U1.7 (GND), U2.11 (V-), U3.4 (V-), U4.15 (GND), U4.21 (GND), U6.2 (GND), U7.3 (A), U8.4 (GND1), U10.2 (VIN), U12.1 (A1), U12.2 (A0), U12.7 (GND)
GNDA: C14.2, C15.2, C16.2, C19.2, D8.2 (A2), D15.2 (A2), D16.2 (A), D17.2 (A2), D18.2 (A2), J1.1, J1.2, JP1.2 (B), Q19.3 (C), Q20.3 (S), R32.2, R50.2
GND_RS485: C33.2, C34.2, C38.2, C39.2, D21.1 (A1), D22.1 (A1), J15.4, J16.4, R70.2, U8.5 (GND2), U9.3, U10.3 (0V), U11.5 (GND)
GND_VOLTAGE_DROP_ADC: R57.1, U4.28 (P6)
GND_VOLTAGE_DROP_INPUT: J12.3, R52.2
LED1_PF6_RST: J13.2, R1.2, U4.18 (PF6(RST))
unnamed: C9.1, R36.2
unnamed: C19.1, R55.2
unnamed: D1.1 (K), R2.2
unnamed: D2.1 (K), R4.2
unnamed: D7.2 (A2), D8.1 (A1), R26.2, U1.3
unnamed: D9.1 (A1), D10.1 (A1), Q12.1 (G), R33.1
unnamed: D11.1 (A1), J7.2, Q12.2 (D), R36.1
unnamed: D12.2 (A2), J8.2, Q15.3 (D)
unnamed: D13.2 (A2), J9.2, Q16.3 (D)
unnamed: D14.2 (A2), D15.1 (A1), R46.2, U1.6
unnamed: D16.1 (K), D17.1 (A1), Q20.1 (G), R51.1
unnamed: D18.1 (A1), J11.2, Q20.2 (D), R55.1
unnamed: C35.1, D23.1 (K), R71.2, U12.10 (Vin+)
unnamed: C35.2, D24.1 (K), R72.2, R74.1, U12.9 (Vin-)
unnamed: C36.1, D25.1 (K), R73.2, R74.2, U12.8 (Vbus)
unnamed: J4.2, R25.2, U2.10 (+)
unnamed: J5.2, R22.2, U2.12 (+)
unnamed: J6.2, R21.2, U2.5 (+)
unnamed: J6.3, R24.2, U2.3 (+)
unnamed: F3.2, J10.1, J10.2
unnamed: F4.1, MOD1.4 (OUT+)
unnamed: Q1.1 (B), R1.1
unnamed: Q1.3 (C), R2.1
unnamed: Q2.1 (B), R3.1
unnamed: Q2.3 (C), R4.1
unnamed: Q9.1 (B), R26.1
unnamed: Q9.2 (E), R32.1
unnamed: Q9.3 (C), Q10.1 (B), Q11.1 (B), R31.2
unnamed: Q10.2 (E), Q11.2 (E), R33.2
unnamed: Q13.1 (B), R34.2
unnamed: Q13.3 (C), R37.1, R39.1
unnamed: Q14.1 (B), R35.2
unnamed: Q14.3 (C), R38.1, R40.1
unnamed: Q15.1 (G), R39.2
unnamed: Q15.2 (S), R41.1, R43.1
unnamed: Q16.1 (G), R40.2
unnamed: Q16.2 (S), R42.1, R44.1
unnamed: Q17.1 (B), R46.1
unnamed: Q17.3 (C), Q18.1 (B), Q19.1 (B), R49.2
unnamed: Q17.2 (E), R50.1
unnamed: Q18.2 (E), Q19.2 (E), R51.2
unnamed: Q21.1 (B), R65.2
unnamed: Q21.3 (C), R66.1
unnamed: R56.1, R57.2, U3.7
unnamed: R66.2, U9.2
unnamed: R28.1, U2.1, U2.2 (-)
unnamed: R27.1, U2.6 (-), U2.7
unnamed: R30.1, U2.8, U2.9 (-)
unnamed: R29.1, U2.13 (-), U2.14
unnamed: C17.1, R47.2, R48.1, U3.3 (+)
unnamed: R53.2, U3.1, U3.2 (-)
unnamed: R52.1, R53.1, U3.5 (+)
unnamed: R54.1, R56.2, U3.6 (-)
unnamed: R62.1, R64.1, U5.1 (ADJ)
unnamed: R67.2, U9.4, U11.2 (~RE), U11.3 (DE)
unnamed: U8.6 (VOB), U11.4 (DI)
unnamed: U8.7 (VIA), U11.1 (RO)
PWM_FAN_BALANCER: R34.1, U4.24 (PA2)
PWM_FAN_SMPS: R35.1, U4.25 (PA3)
PWM_OUT_CHRG: J2.3, U4.16 (PF0)
PWM_OUT_DISCH: J2.2, U4.17 (PF1)
RS232_RX: U4.23 (PA1), U8.2 (VOA)
RS232_TX: U4.22 (PA0), U8.3 (VIB)
RS485_OUTPUT_ENABLE: R65.1, U4.12 (PD6)
R_shunt_H: J3.2, R72.1
R_shunt_L: J3.1, R71.1
SDA: R75.2, U4.4 (PC2), U12.4 (SDA)
TEMP_AKU_12V: R28.2, U4.8 (PD2)
TEMP_AKU_24V: R27.2, U4.9 (PD3)
TEMP_BALANCER: R30.2, U4.11 (PD5)
TEMP_SMPS: R29.2, U4.10 (PD4)
UPDI: J14.2, R61.2, U4.19 (PF7(UPDI))
VOLTAGE_BATT_12V: C23.1, R59.2, R60.1, U4.7 (PD1)
VOLTAGE_BATT_24V_3W: J12.2, R73.1
VREF: C25.1, C28.1, R47.1, R63.2, U4.13 (PD7), U7.1 (REF), U7.2 (K)

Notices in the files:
software/Balancer-AVR.X/mcc_generated_files/system/src/pins.c:
© [2025] Microchip Technology Inc. and its subsidiaries.
